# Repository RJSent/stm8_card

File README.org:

#+TITLE: stm8_card
#+AUTHOR: Richard Sent

* Overview

This is a work-in-progress project for an STM8 microcontroller powered
business card. I am using an STM8 alongside a OLED with a SSD1306
controller.

I've finished implementing most basic functionality (UART, I2C, etc)
and have begun working on the business card proper. There's still a
fair amount of work left to do. In particular, I need to implement
timers (instead of ~delay~), user input (debounced buttons), and a
low-power mode using interrupts. Of course, there's also more to be
done regarding the display itself!

I working to keep most of my code generic enough that I can reuse it
in future projects without needing to rework everything. It will act
as a miniature library of sorts for me to use. When that happens I
might move that to a different git project, and leave business card
specific code here.

[[file:media/20210215_153346_scaled.jpg]]

[[file:media/lasers_scaled.jpg]]

[[file:media/working_lasers.mp4][Here's a demonstration of a work in progress space invaders game!]] We
can see that the player ship and lasers are functional and fully
animated. If you want to see the work that led up to this so far,
check out the media folder!

* License

This project is available under the terms of the [[https://opensource.org/licenses/MIT][MIT License]].

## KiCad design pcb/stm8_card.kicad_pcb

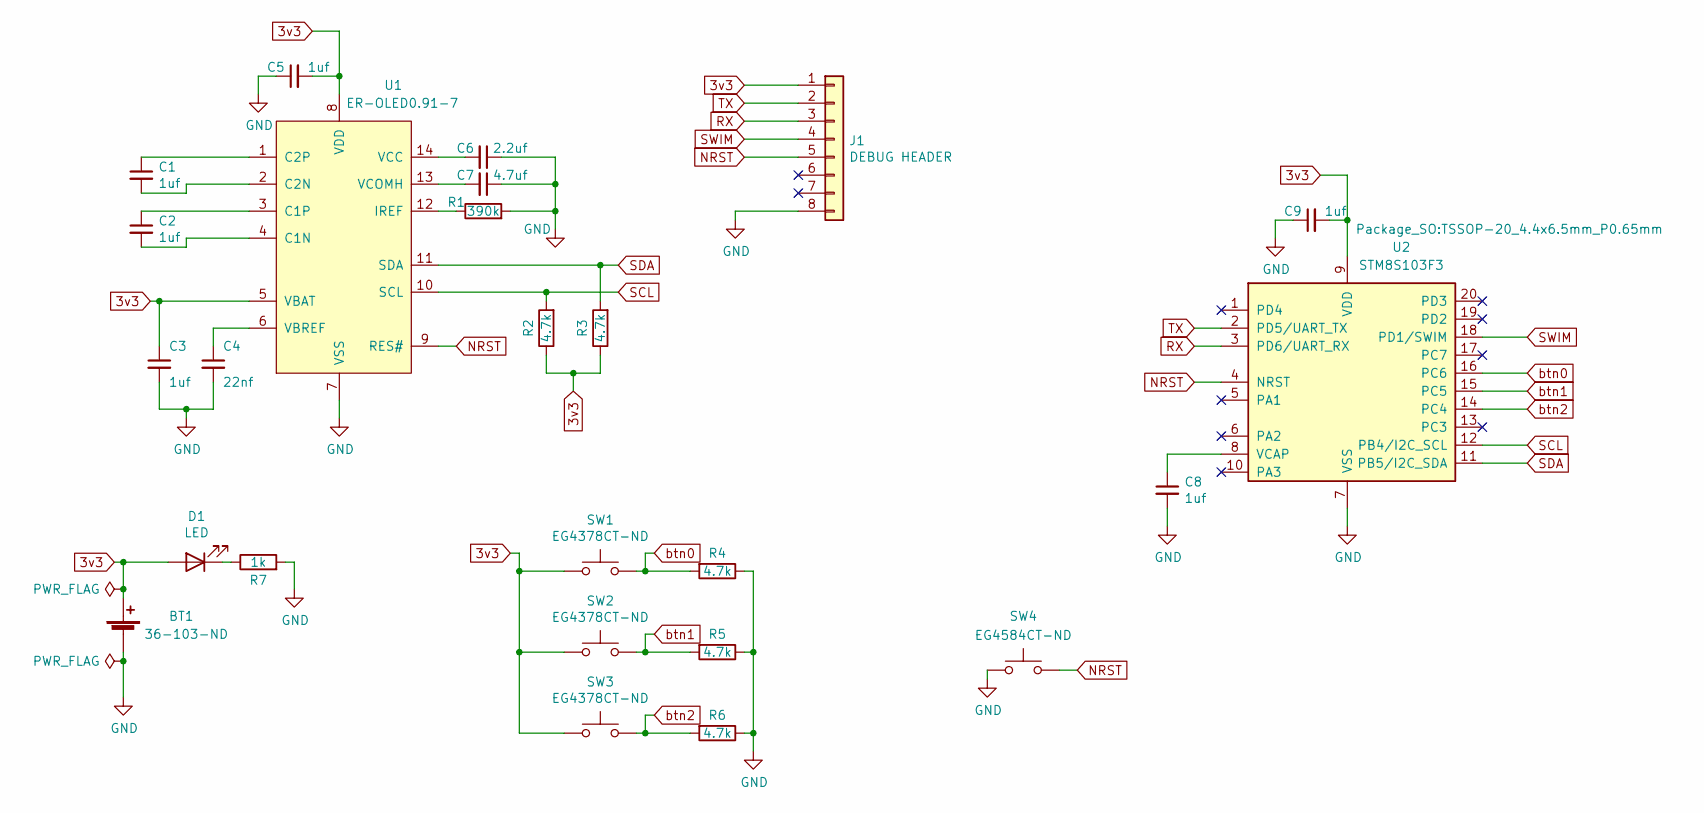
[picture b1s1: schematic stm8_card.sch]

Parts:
BT1: 103; BatteryHolder_Keystone_103_1x20mm_Corrected; digikey 36-103-ND
C1, C2, C3, C5, C8, C9: 1uf; C_0805_2012Metric_Pad1.18x1.45mm_HandSolder
C4: 22nf; C_0805_2012Metric_Pad1.18x1.45mm_HandSolder
C6: 2.2uf; C_0805_2012Metric_Pad1.18x1.45mm_HandSolder
C7: 4.7uf; C_0805_2012Metric_Pad1.18x1.45mm_HandSolder
D1: LED; LED_0805_2012Metric_Pad1.15x1.40mm_HandSolder; digikey 404-1316-1-ND
J1: DEBUG HEADER; 2mm_2x4_ICSP
R1: 390k; R_0805_2012Metric_Pad1.20x1.40mm_HandSolder
R2, R3, R4, R5, R6: 4.7k; R_0805_2012Metric_Pad1.20x1.40mm_HandSolder
R7: 1k; R_0805_2012Metric_Pad1.20x1.40mm_HandSolder
SW1, SW2, SW3: TL59AF100Q; digikey EG4378CT-ND
SW4: TL3302AF260QG; digikey EG4584CT-ND
U1: ER-OLED0.91-7
U2: STM8S103F3; TSSOP-20_4.4x6.5mm_P0.65mm

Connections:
3v3: BT1.1 (+), C3.1, C5.2, C9.2, D1.2 (A), J1.1, R2.1, R3.1, SW1.1, SW2.1, SW3.1, U1.5 (VBAT), U1.8 (VDD), U2.9 (VDD)
GND: BT1.2 (-), C3.2, C4.2, C5.1, C6.1, C7.1, C8.2, C9.1, J1.8, R1.2, R4.1, R5.1, R6.1, R7.2, SW4.1, U1.7 (VSS), U2.7 (VSS)
NRST: J1.5, SW4.2, U1.9 (RES#), U2.4 (NRST)
unnamed: C1.1, U1.1 (C2P)
unnamed: C1.2, U1.2 (C2N)
unnamed: C2.1, U1.3 (C1P)
unnamed: C2.2, U1.4 (C1N)
unnamed: C4.1, U1.6 (VBREF)
unnamed: C6.2, U1.14 (VCC)
unnamed: C7.2, U1.13 (VCOMH)
unnamed: C8.1, U2.8 (VCAP)
unnamed: D1.1 (K), R7.1
unnamed: R1.1, U1.12 (IREF)
RX: J1.3, U2.3 (PD6/UART_RX)
SCL: R2.2, U1.10 (SCL), U2.12 (PB4/I2C_SCL)
SDA: R3.2, U1.11 (SDA), U2.11 (PB5/I2C_SDA)
SWIM: J1.4, U2.18 (PD1/SWIM)
TX: J1.2, U2.2 (PD5/UART_TX)
btn0: R4.2, SW1.2, U2.16 (PC6)
btn1: R5.2, SW2.2, U2.15 (PC5)
btn2: R6.2, SW3.2, U2.14 (PC4)

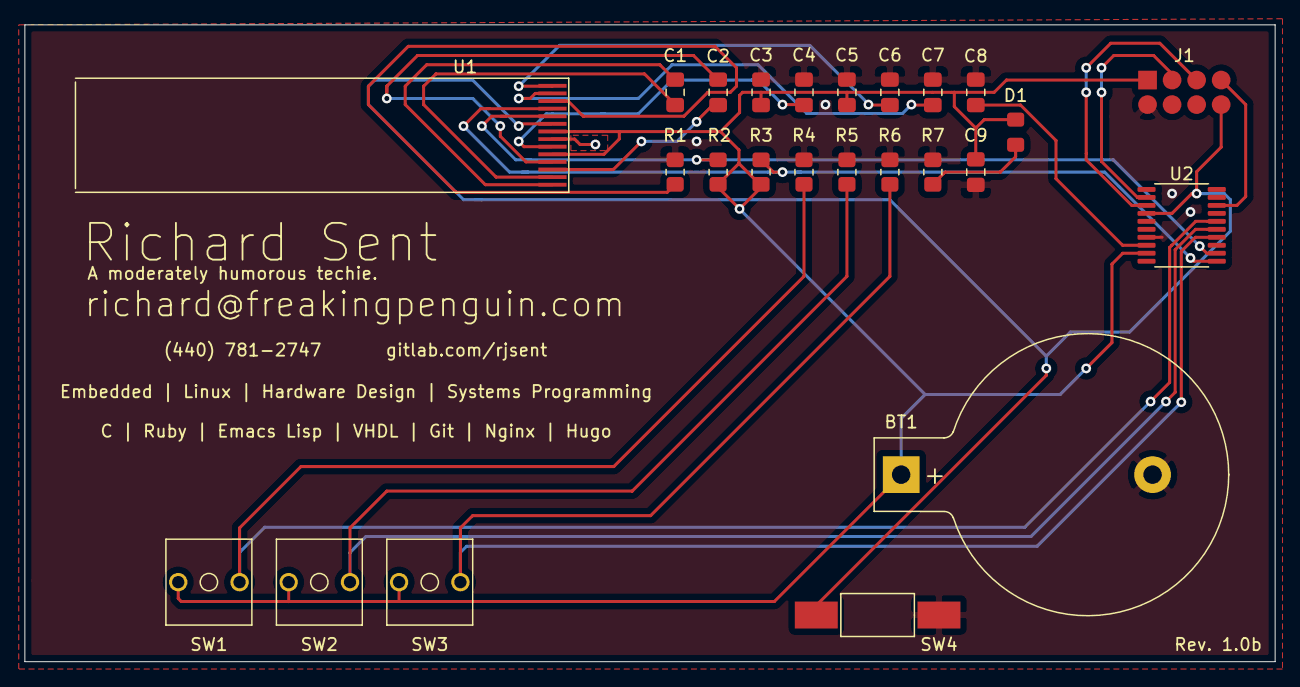
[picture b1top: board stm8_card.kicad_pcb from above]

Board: 2 copper layers, 101.9 x 51.9 mm, 25 parts (0 on the bottom side), 21 nets.

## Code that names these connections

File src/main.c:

#include <stdlib.h>

#include "baseline.h"
#include "i2c.h"
#include "uart.h"
#include "ssd1306.h"
#include "image.h"
#include "space_invader.h"
#include "gpio.h"

gpio_pin_t btn0 = { .port = 'C', .num = 6 };
gpio_pin_t btn1 = { .port = 'C', .num = 5 };
gpio_pin_t btn2 = { .port = 'C', .num = 4 };
gpio_pin_t led0 = { .port = 'A', .num = 1 };
gpio_pin_t led1 = { .port = 'A', .num = 2 };

static void initialize_gpio() {
  gpio_mode(&btn0, GPIO_INPUT_FLOAT);
  gpio_mode(&btn1, GPIO_INPUT_FLOAT);
  gpio_mode(&btn2, GPIO_INPUT_FLOAT);
  gpio_mode(&led0, GPIO_OUTPUT_PUSH_PULL);
  gpio_mode(&led1, GPIO_OUTPUT_PUSH_PULL);
}

/* TODO: move to power saving.c/h and take struct for what to gate */
static void periph_gating() {
  *CLK_PCKENR1 &= 0x1;           /* only i2c enabled */
  // *CLK_PCKENR1 |= 1 << 3;        /* enable uart1 */
  *CLK_PCKENR2 &= !(0x8C);      /* 0 to everything not reserved, rm0016 pg 96 */
}

static void power_saving() {
  clk_hsi_prescaler(1);
  clk_cpu_prescaler(128);        /* 125 kHz cpu */
  periph_gating();
  
}

static void initialize() {
  const int baud_rate = 9600;
  const long fmaster = 16000000;

  power_saving();

  uart_init(baud_rate, fmaster);
  i2c_init(2);
  initialize_gpio();
  ssd1306_init(SSD1306_I2C);
  invader_game_init(SSD1306_WIDTH, SSD1306_HEIGHT);
}

int main() {
  initialize();
  uart_printf("%s\n\r", __DATE__);
  char cycle_num = 0;
  const char max_cycles = 10;

  while (1) {
    /* uart_printf("-----CYCLE %d-----\n\r", cycle_num); */
      struct InvaderCommands invader_commands;
      if (gpio_read(&btn0)) {
	gpio_write(&led0, true);
	gpio_write(&led1, false);
	invader_commands.movement = DOWN;
      } else if (gpio_read(&btn1)) {
	gpio_write(&led0, false);
	gpio_write(&led1, true);
	invader_commands.movement = UP;
      } else {
	gpio_write(&led0, false);
	gpio_write(&led1, false);
	invader_commands.movement = NOP;
      }
      /* debounded input here. Maybe just have as timer though for
	 extra button to exit */
      if (random_upto(32) > 30) {
	invader_commands.shoot = TRUE;
      }
      struct DrawableImage *spaceship = debug_drawableimage_spaceship();
      invader_game_tick(&invader_commands);
      draw_image(spaceship, LEFT);
      struct DrawableImage *lasers[3];
      struct DrawableImage *invader_lasers[3];
      struct DrawableImage *invaders[3];
      for (int i = 0; i < 3; i++) {
	lasers[i] = debug_drawableimage_playerlaser(i);
	invader_lasers[i] = debug_drawableimage_invaderlaser(i);
	invaders[i] = debug_drawableimage_invader(i);
	draw_image(lasers[i], LEFT);
	draw_image(invader_lasers[i], LEFT);
	draw_image(invaders[i], LEFT);
      }
      draw_half(LEFT);
      clear_buffer();
      for (int i = 0; i < 3; i++) {
	draw_image(lasers[i], RIGHT);
	draw_image(invader_lasers[i], RIGHT);
	draw_image(invaders[i], RIGHT);
      }
      draw_half(RIGHT);
      clear_buffer();
      invader_commands.shoot = FALSE;
      /* delay(2000); */

    cycle_num++;

    /* if (cycle_num == max_cycles) { */
    /*   uart_printf("-----END-----\n\r"); */
    /* while(1) {}; */
    /* } */
    
    clear_buffer();    
  }
}

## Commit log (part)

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2020-12-04 Initial commit + Blinky debug code functionality
2020-12-04 Added dir_locals so flycheck finds correct libraries
2020-12-08 Splitting across multiple files
2021-02-01 UART transmission is functional with 9600 baud rate
2021-02-02 Add LICENSE
2021-02-02 Added basic readme
2021-02-05 functioning uart_printf with numbers
2021-02-05 clk prescaler functions, currently in baseline
2021-02-05 Register file update
2021-02-05 Cleaned up main + more uart format options
2021-02-05 modified makefile to be a bit more adaptable
2021-02-05 gitignore update
2021-02-05 removed 2nd title as header
2021-02-05 Prep work for i2c and ssd1306
2021-02-05 ssd1306.h basic structure
2021-02-06 Removed ascii_to_int for stdlib atoi
2021-02-13 Partially sorta kinda functional I2C code
    Managed to get it working with sending a
    I2C address and getting an ACK. I made some
    small changes that I can't recall and suddenly
    it isn't succeeding at that.
2021-02-13 fixed i2c issue
    Needed a small delay between start_cond and send_byte. Need a better
    solution with a guard in send_byte of some kind.
2021-02-14 Fully functioning 1-way I2C communication!
    Currently delay between sending addr is hardcoded. Definitely needs
    changing since the frequency might not be consistent.
2021-02-14 some tidying up
2021-02-14 fixed issue when i2c_send_bytes() called too quickly
    the start condtion now isn't sent until the bus is free
2021-02-14 i2c NACK_ERROR guard + consistent transmission w/o hardcoded delay
2021-02-14 Partial work on SSD1306 communication
2021-02-14 Further debugging i2c issue
2021-02-15 photo of working screen
2021-02-15 changed mux ratio + trying to display hello world manually
2021-02-15 hello world gimp image
2021-02-15 CMD_HW_COM_PINS_CONFIG + 0x12 is almost certaintly the wrong setting.
    What should be 4 pixels tall is just 2.
2021-02-15 Successfully printed an image to the display!!!
    I used https://javl.github.io/image2cpp/ to generate the byte array,
    using the "vertical - 1 bit per pixel" setting.
2021-02-15 roommate art
2021-02-15 slight fix to image size hopefully
2021-02-15 Only way I could figure out scaling that gitlab accepts
2021-02-15 typo
2021-02-15 Cleaned up, removed commented code, increased delay to lower flicker
2021-02-18 implementation of ssd1306_protocol + scaffolding for draw_pixel
2021-02-20 printed compilation date on boot
2021-02-20 experimenting with adding a framebuffer and drawing in two steps
2021-02-20 demo of two synced advancing lines on each half of screen
2021-02-21 added const keyword to i2c_send_bytes due to warning. Maybe remove?
2021-02-21 demonstration code + video showing framebuffer use
2021-02-21 attached videos
2021-02-21 Added description as it's not embedded with Gitlab org
2021-02-21 added todo + refactored clear_display
2021-02-21 condensed dump targets in the makefile into one
2021-02-21 changed size from char to int in i2c_send_bytes and send_data
2021-02-21 removed unneeded delay
2021-02-21 apparently functional draw_pixel code.
    I coded this in like 5 minutes and knew it would work at the time with
    minimal debugging. Looking back, I'm confused as to how I figured
    this out...
2021-02-21 demonstration code for draw_pixel
2021-02-21 draw_pixel demonstration video, a blinking face
2021-02-21 replaced some hardcoded numbers with existing macros
2021-02-21 added explanation + warning about ssd1306 struct S
2021-02-21 added 2nd comment about packing, not needed
2021-02-22 removed unneeded printf + old todo
2021-02-22 cleaned up smile demo + demoed invert_display
2021-02-22 scaled some images to be smaller + invert_buffer demo
2021-02-22 added mirror_buffer function
2021-02-22 functioning mirror_buffer
2021-02-22 small changes to baseline Noticed odd behavior with unpushed changes
    Prescaler or clk divider or something wasn't set correctly. I thought
    all I had done with change returns to chars instead of ints, and
    change arguments to chars that didn't need the int memory. Maybe
    there's a deeper I need to find
2021-02-22 x axis mirror demo
2021-02-22 demo of mirroring both
2021-02-22 updated readme + new demo
2021-02-22 decreased return values to char instead of ints
2021-02-22 added random element to this demo code cause it looks cool. :)
2021-02-22 changed draw_pixel to set_pixel
2021-02-22 added flip_pixel method, current value of pixel is inverted
2021-02-23 added codeviz graph_deps
2021-02-26 partially functional code to draw arbitrary animated images
2021-02-26 more functional draw_image code. Not drawing 100% perfectly.
    i.e. 0x23 is actually drawing 1100_0100 instead of 0010_0011
2021-02-26 tiny changed to draw_image
2021-02-26 working draw_image + associated structs!!!
2021-02-26 readme update
2021-02-27 now supports images with widths not a multiple of 8
2021-02-27 removed uart dependency from i2c
2021-02-27 modified some return types, maybe would reduce memory use
2021-02-27 drawing image moving across screen demo!
2021-02-27 replaced draw_right_half and draw_left_half with draw_half
2021-02-27 removed address argument to ssd1306.c/send_bytes
2021-02-27 added boolean type
2021-02-27 tidied up code + change set_pixel back to draw_pixel
2021-02-27 space_invader outlining. Worried about memory issues
2021-02-28 work on game structs
2021-02-28 adjusted code to remove standard features SDCC doesn't support :(
2021-02-28 some utility math functions in baseline
2021-02-28 useful macro
2021-02-28 working on debugging space_invader.c/h
2021-02-28 demo code for spaceship movement
2021-02-28 partially functional shoot_laser and laser_tick code
2021-02-28 working lasers!!!!!! :D
2021-02-28 added comment about interesting issue
2021-02-28 removed uart + some more commenting
2021-02-28 slowed gain of velocity to try and give ship more weight
2021-02-28 added fixem
2021-03-01 reworked ticks between velocity gains + debugging code
2021-03-01 added todo
2021-03-02 nonfunctional skeleton for invader enemies
2021-03-03 fixed bug with my invader... typed i insted of ii
    also what the heck is up with sdcc suddenly complaining about resuing
    symbols now as opposed to before?
2021-03-03 adjusted speed to make it visually pleasing. Not balanced yet.
2021-03-03 removed inaccurate comment + made change that shouldn't matter
2021-03-03 apparently I modified the animation? Maybe forgot to save earlier
2021-03-03 working towards invaders shooting lasers
2021-03-03 added image.c/h function to say if two drawableimages overlap
2021-03-03 more untested work on invader lasers
2021-03-03 begun testing code to debug issues with invaderlaser
2021-03-03 debug code to verify i'm not running out of memory. i think i am D:
2021-03-03 decrease maximum number of animation frames
2021-03-03 fixed bug with invader_lasers not working properly.
    Just missed stuff copying logic. Probably a sign i need to create
    smaller methods designed for working with the laser arrays
2021-03-03 video showing invader lasers
2021-03-03 noticed problem in makefile, added readme
2021-03-04 commented on some interesting behavior I noticed
2021-03-04 fixed error with main target not having rule b/c no header file
2021-03-04 noticed odd behavior/padding in main.map, tried figuring it out
2021-03-04 scaffolding for check_collisions
2021-03-10 work on explosion invaders
2021-03-10 unfinished work on invader_explosion
2021-03-11 fixed invader collision code! Still need to do something about score
2021-03-11 adjusted %s + added delay in ticks between invader spawns!
2021-03-11 removed old code + got rid of check_collisions, put into game_tick
2021-04-06 tried creating new makefile and project structure
    New errors pop up that never have before. Additionally the size of the
    final executable is larger than before. In fact, it's too large to
    flash to the microcontroller.
2021-04-06 fixed final exe being too large + new errors
    problem was not including cflags when compiling, particularly the
    family of the chip.
    Presumably specifying the family tells sdcc int literals can be
    converted to pointers & lets it perform some code size optimizations
    it can't do otherwise. (It also may not have been a valid exe without
    the family flag during compile time. Since I couldn't flash it b/c
2021-04-06 moved build dir rule loop
2021-04-06 alignment + expansion at assignment instead of use where possible
2021-04-06 fixed flash target + rearranged targets alphabetically
2021-04-06 comment
2021-04-06 moved parts of gitignore to build directory
2021-04-06 added fixme
2021-04-18 gitignore
2021-04-18 gpio untested
2021-04-18 gpio replace stdlib with stdint + make function static
2021-04-18 removed blink code, not really fit for library or final project
2021-04-18 adjusted main to test gpio, compilation fails
    Not 100% sure of compilation file, but I know it's not an sdcc version
    change. I checked out before branch, no issues. Could either be code
    or ?maybe? makefile. haven't checked
2021-04-18 fixed dir-locals. Both wrong format and wrong name >.<
2021-04-19 trying to fix pd1 cr1 issue
    see comment in main
2021-04-20 "fixed" the gpio io issue + removed some code from registers
    TURNS OUT THERE WASN'T AN ISSUE AT ALL.
    PD1 is shared with SWIM, which is an active low communication
    protocol. I had the programmer connected to the SWIM pin, which has a
    separate header. When the SWIM cable is connected, the programmer
    brings that pin high, causing the LED I was using to try and verify if
    the pull-up was working to turn on. GPIO code is fully functional.
2021-04-20 removed some comments from main. goto this commit to see them
2021-04-20 identified indirect cause of corruption issue
    Actually I don't even know at this point. Messing around with printfs
    ALSO fixed the issue, EVEN WHEN THE PRINTF IS RIGHT AFTER UART_INIT().
    YOU KNOW, THE 4TH LINE OF CODE TO BE EXECUTED!!
2021-04-20 alternative fix to that doesn't require padding
    i dont even know honestly
2021-04-20 fixed the gd issue
    in space_invader.c, I have some debug methods that return
    drawable_image's until I can decide on a better method.
    These methods will return NULL if the image should not be drawn.
    My draw_image() code had some error checking to make sure the position
    was valid, the size was valid, etc.
    When I had 16 bytes of padding at 0x1, just 1 byte off of NULL, the
2021-04-20 added comment about fix to main
2021-04-20 moved ticks_until_gain into player_ship struct
    makes more sense there imo
2021-04-20 space invader replaced 0 returns with NULL
2021-04-20 adjusted main loop to be less redundant
    "sub-cycle" based testing no longer needed
2021-04-20 fixed operator precendence order causing wrong gpio_read result
2021-04-20 changed return 0 to return null
2021-04-20 video showing null pointer glitch in 157fd06
2021-04-20 removed main comments + added goal
2021-04-20 removed more main comments, go here to see them
2021-04-20 moved some code to initialize() method
2021-04-20 minor main edit
2021-04-20 added dir-locals fixme
2021-04-21 invader adjusted velocity parameters to have more "weight"
2021-04-22 pcb incomplete draft schematic
2021-04-22 pcb finished first schematic revision
2021-04-22 pcb one less backup file
2021-04-22 pcb added missing ground
2021-04-22 pcb capitalized stm8s103f3
2021-04-22 pcb improved schematic
2021-04-22 pcb added 0805 handsolder footprints to C and R
2021-04-22 pcb debug icsp footprint
2021-04-22 pcb footprint for eg4378ct-nd
2021-04-22 pcb actually applied sw footprints
2021-04-22 dunno what this is
2021-04-22 pcb board wip
2021-04-22 pcb corrected battery holder schematic to have closed perimeter
2021-04-22 pcbupdates
2021-04-22 updated dimensions
2021-04-22 pcb technically finished I think?
2021-04-22 pcb more work on card
2021-04-22 pcb readded ground planes
2021-04-22 pcb hid ground via under mcu
2021-04-22 pcb moved some vias a tiny bit
2021-04-22 moved a singular via
2021-04-23 small edits, still need to correct cap issue also add led + res
2021-04-23 pcb improved pcb + added led, res, and mcu cap
2021-04-23 pcb improvements
2021-04-23 pcb cache update?
2021-04-24 pcb adjusted back btn traces
2021-04-24 pcb adjusted front btn routes + other small edits
2021-04-24 pcb removed 2 vias
2021-04-24 pcb idk what i did
2021-04-24 pcb centered some traces between c and rs
2021-04-24 pcb adjusted trace spacing
2021-04-24 pcb ssd1306 routing
2021-04-24 pcb small alignment + redundant traces
2021-04-25 pcb slightly moved silk text
2021-04-25 pcb apparently some changes idk
2021-05-22 rescued schematic library to newer version I think???
2021-05-23 fixed bug with ckdivr setting in baseline clearing bits
2021-05-23 lowered cpu prescaler, can probably drop hsi if code optimized
2021-05-23 lowered charge pump, ~ 0.1mA
2021-05-23 saved another 0.6mA with periph gating
2021-05-24 rough schematic update
2021-07-02 added card demo video
2021-08-29 rev 1.0b
